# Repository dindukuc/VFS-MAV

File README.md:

# VFS-MAV

This Repo contains the code for the VFS-MAV team 2019-2020

The code includes testing and debugging programs.

The latest set of code that we used is contained in the "MAV_FC_V2-1" folder

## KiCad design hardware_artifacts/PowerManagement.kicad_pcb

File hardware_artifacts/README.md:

### This directory contains the hardware schematics and PCB files

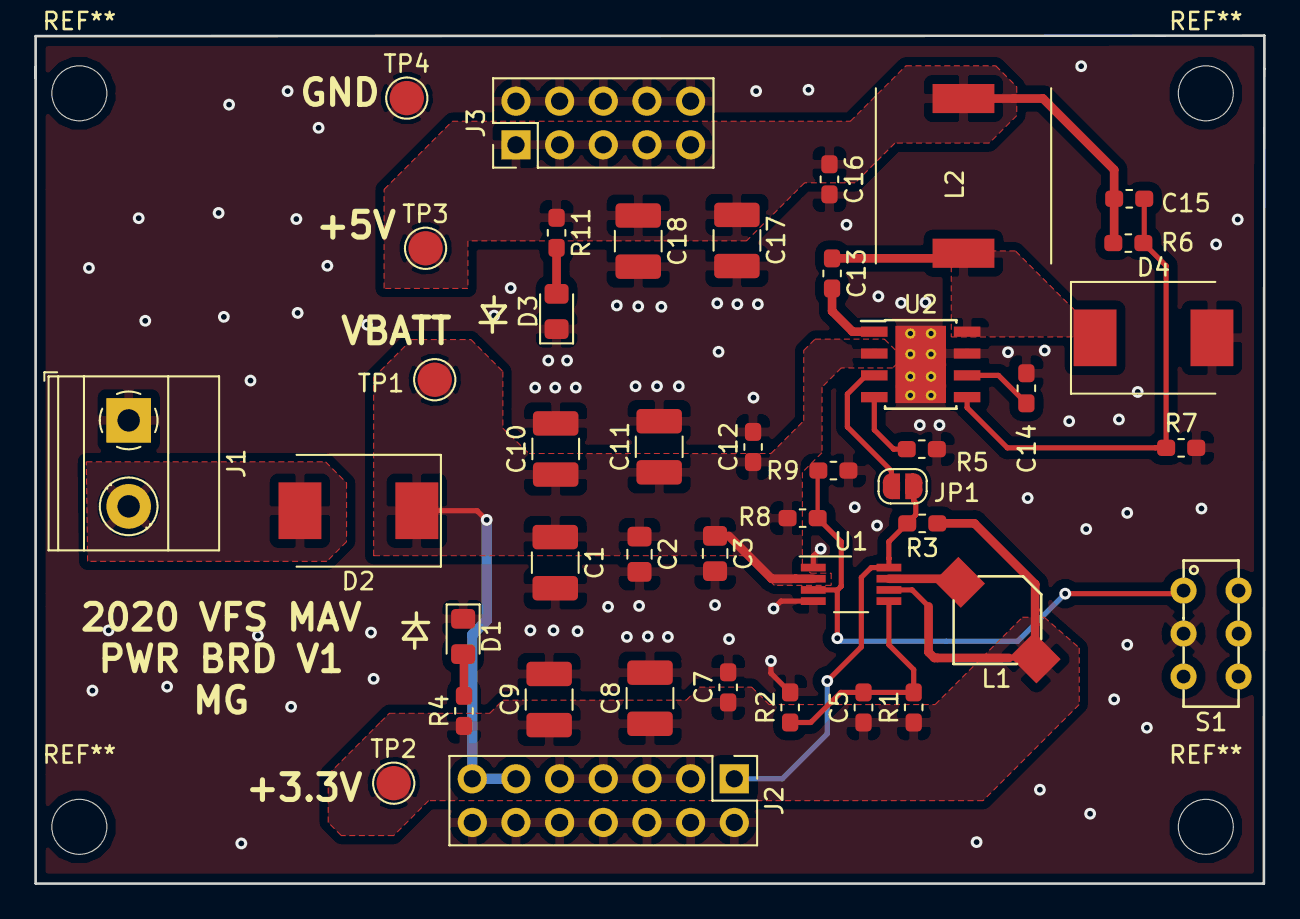
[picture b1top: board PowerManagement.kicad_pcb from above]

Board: 2 copper layers, 71.5 x 49.3 mm, 43 parts (0 on the bottom side), 17 nets.

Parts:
C1, C8, C9, C17, C18: 22uF; C_1210_3225Metric_Pad1.42x2.65mm_HandSolder
C2, C3: 10uF; C_0805_2012Metric_Pad1.15x1.40mm_HandSolder
C5: Cff; C_0603_1608Metric_Pad1.05x0.95mm_HandSolder
C7, C12, C16: 1uF; C_0603_1608Metric_Pad1.05x0.95mm_HandSolder
C10, C11: 4.7uF; C_1210_3225Metric_Pad1.42x2.65mm_HandSolder
C13: .1uF; C_0603_1608Metric_Pad1.05x0.95mm_HandSolder
C14: 22nF; C_0603_1608Metric_Pad1.05x0.95mm_HandSolder
C15: 330pF; C_0603_1608Metric_Pad1.05x0.95mm_HandSolder
D1, D3: LED; LED_0805_2012Metric_Pad1.15x1.40mm_HandSolder
D2, D4: CDBC540-G; D_SMC
J1: Screw_Terminal_01x02; TerminalBlock_Phoenix_MKDS-1,5-2_1x02_P5.00mm_Horizontal
J2: Conn_02x07_Odd_Even; PinHeader_2x07_P2.54mm_Vertical
J3: CONN_02X05; PinHeader_2x05_P2.54mm_Vertical
JP1: SolderJumper_2_Open; SolderJumper-2_P1.3mm_Open_RoundedPad1.0x1.5mm
L1: 3.3uH; L_Sumida_4.9x4.9mm_diag
L2: 4.7uH; L_TDK_VLF10040
R1: 562k; R_0603_1608Metric_Pad1.05x0.95mm_HandSolder
R2, R8: 180k; R_0603_1608Metric_Pad1.05x0.95mm_HandSolder
R3: 10k; R_0603_1608Metric_Pad1.05x0.95mm_HandSolder
R4: 1.2k; R_0603_1608Metric_Pad1.05x0.95mm_HandSolder
R5: 20k; R_0603_1608Metric_Pad1.05x0.95mm_HandSolder
R6: 68k; R_0603_1608Metric_Pad1.05x0.95mm_HandSolder
R7: 12k; R_0603_1608Metric_Pad1.05x0.95mm_HandSolder
R9: 80k; R_0603_1608Metric_Pad1.05x0.95mm_HandSolder
R11: 2.71k; R_0603_1608Metric_Pad1.05x0.95mm_HandSolder
S1: SPDT_MHSS1104
TP1, TP2, TP3, TP4: TestPoint; TestPoint_Pad_D2.0mm
U1: TPS62160; VSSOP-8_3.0x3.0mm_P0.65mm
U2: LMR14050; TI_SO-PowerPAD-8_ThermalVias

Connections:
+3V3: C5.1, C7.1, C8.1, C9.1, J2.3, J2.5, J2.7, J2.9, L1.2, R1.1, R3.1, R4.1, TP2.1, U1.6
+5V: C15.1, C16.1, C17.1, C18.1, J3.1, J3.3, J3.5, J3.7, J3.9, L2.2, R6.2, R11.1, TP3.1
+BATT: C1.1, C2.1, C3.1, C10.1, C11.1, C12.1, D2.1, J2.11, J2.13, R8.1, TP1.1, U1.2, U2.2
Earth: C1.2, C2.2, C3.2, C7.2, C8.2, C9.2, C10.2, C11.2, C12.2, C14.2, C16.2, C17.2, C18.2, D1.1, D3.1, D4.2, J1.1, J2.2, J2.4, J2.6, J2.8, J2.10, J2.12, J2.14, J3.2, J3.4, J3.6, J3.8, J3.10, R2.2, R5.1, R7.2, R9.1, S1.2, TP4.1, U1.1, U1.4, U2.7, U2.9
MCU_ENABLE: J2.1, JP1.1, R3.2, U1.8
unnamed: C5.2, R1.2, R2.1, U1.5
unnamed: C13.1, D4.1, L2.1, U2.8
unnamed: C13.2, U2.1
unnamed: C14.1, U2.6
unnamed: C15.2, R6.1, R7.1, U2.5
unnamed: D1.2, R4.2
unnamed: D2.2, J1.2
unnamed: D3.2, R11.2
unnamed: JP1.2, U2.3
unnamed: L1.1, U1.7
unnamed: R5.2, U2.4
unnamed: R8.2, R9.2, S1.1, U1.3

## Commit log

2020-02-14 Changed servo limits to use map function
2020-02-14 Changed Servo limits to use map function
    changed initialization of "i" in for loops
    switched left and right servo calculations so they should move the correct way now...hopefully
    Still need to change: map throttle values and linearly scaling offset
2020-02-14 Should've linearly offsetted the slower motor
2020-02-17 Create Controller_RX_Test
2020-02-17 Added test code for receiver alone
2020-02-22 Changed controltest to this file and cleaned it up a bit
2020-02-25 moved files to correct folders
2020-02-25 created and moved file into correct folder
2020-02-27 refactored Control_Test_cleaner into MAV_FC_2.0
2020-02-29 tested refactored code and began fixing pin defs
2020-03-05 Added kill switch functionality and changed yaw offset scaling
2020-03-06 Tuned offset a little bit
    changed it so it controls the lower blade. Still needs to change it bit
2020-03-06 Fixed the controller turning
2020-03-06 fixed filenames
2020-03-06 created version 2.1
2020-03-07 integrated stabilization code into core flight firmware
2020-03-07 updated Core Flight Firmware after review
2020-03-07 integrated and soft-tested the IMU pitch and roll stabilization
2020-03-08 tuning test without pid
2020-03-11 just updating changes
2020-03-12 added interrupt based encoder RPM measurement code
2020-03-13 code to test RPM measurement
2020-03-13 added data_collection program
2020-03-13 updated RPM test code for yaw ramp testing
2022-07-16 Added the power management board and schematic files
